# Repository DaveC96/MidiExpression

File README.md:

# MidiExpression
A hardware unit to add MIDI control to any device that takes an expression pedal input.

This is based on the Arduino Nano, and so only supports DIN MIDI. This project could easily be replicated with a Teensy or similar for USB support.

The board can be powered by:
- USB directly to the Nano
- DC barrel (centre-negative to work with guitar pedalboard PSUs)
- (Speculatively) Directly from the reference voltage on the expression input

-----

## Usage

Upon being powered on, the device will attempt to read any persistent settings. If none are found, it resets to these defaults:

| Param   | Value      |
| :---        | :---          |
| Channel | 0 (omni) |
| CC         | 4            |
| Min value | 0          |
| Max value | 127     |

These can be changed by sending a SysEx message in the following manner:

`[sysex header (0xF0)] [manufacturer ID (0x00)] [channel (0-16)] [CC] [min] [max] [sysex terminator (0xF7)]`

For example, to set channel **12**, CC **42**, with a range of **18**-**99**, the message would be (hex):

`F0 00 0C 2A 12 63 F7`

When receiving a valid sysex config message, the device will reboot to adopt the new parameters.
A hard flash reset for emergenciees can be performed by sending the following (very original) sysex message:

`F0 00 DE AD F7`

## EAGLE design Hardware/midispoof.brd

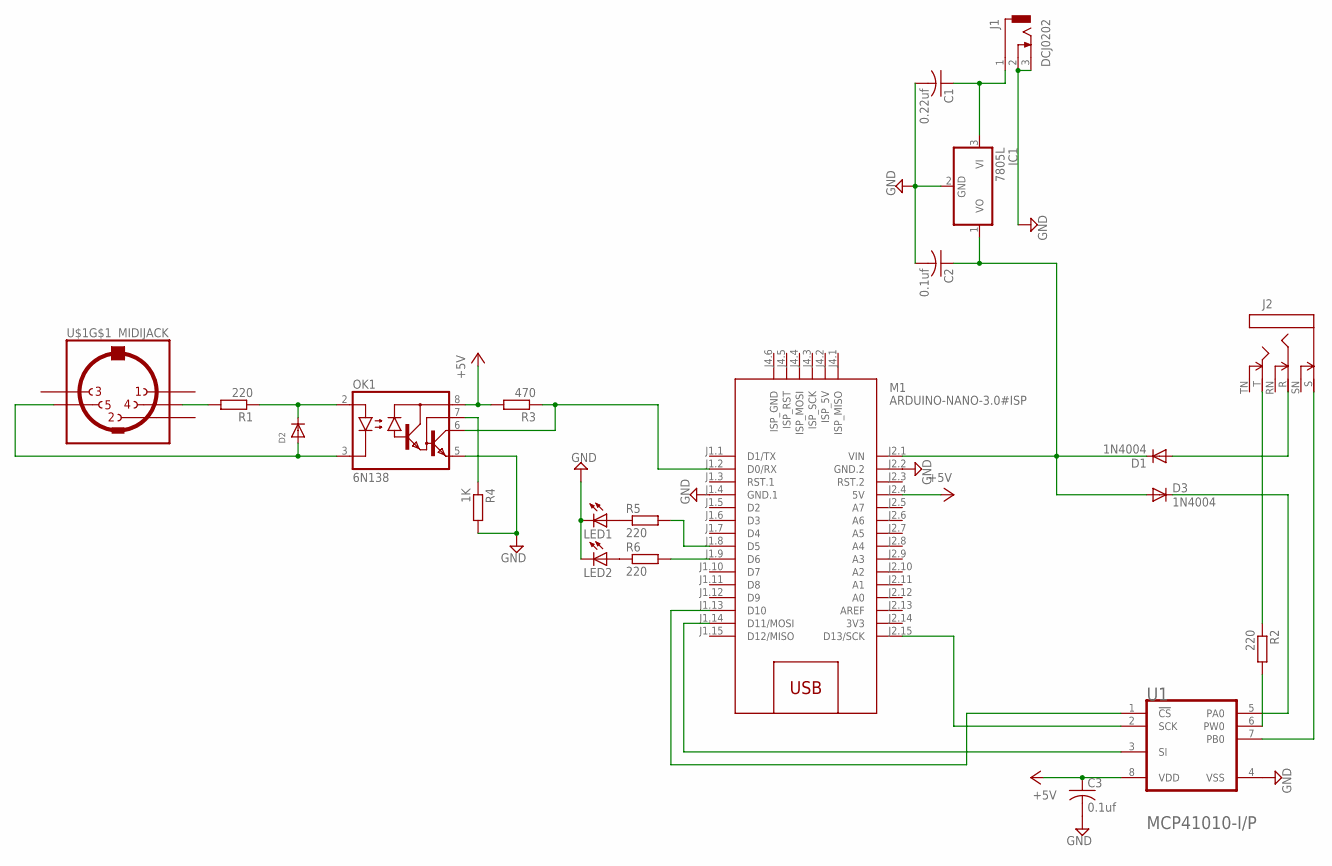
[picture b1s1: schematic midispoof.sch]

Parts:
C1: 0.22uf; C050-025X075
C2, C3: 0.1uf; C050-025X075
D1, D3: 1N4004; DO41-10
D2: DIODEDO-1N4148; DO-1N4148
IC1: 7805L; TO92
J1: DCJ0202
J2: STEREOSWS; NMJ6HC-S
LED1, LED2: LED3MM
M1: ARDUINO-NANO-3.0#ISP
OK1: 6N138; DIL08
R1, R2, R5, R6: 220; 0207/10
R3: 470; 0207/10
R4: 1K; 0207/10
U1: MICROCHIP_MCP41010-I-PMICROCHIP_MCP41010-I-P_0_0; MICROCHIP_MCP41010-I-P_0
U$1: MIDIJACK; CP-2350

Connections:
3V3: M1.J2.14 (3V3)
+5V: C3.1, M1.J2.4 (5V), OK1.8 (VCC), R3.2, U1.8 (VDD)
GND: C1.2, C2.2, C3.2, IC1.2 (GND), J1.2, J1.3, LED1.K (C), LED2.K (C), M1.J1.4 (GND.1), M1.J2.2 (GND.2), OK1.5 (GND), R4.2, U1.4 (VSS)
unnamed: M1.J2.15 (D13/SCK), U1.2 (SCK)
unnamed: C1.1, IC1.3 (VI), J1.1
unnamed: M1.J1.14 (D11/MOSI), U1.3 (SI)
unnamed: LED1.A, R5.1
unnamed: R1.2, U$1.4
unnamed: M1.J1.13 (D10), U1.1 (!CS!)
unnamed: D1.A, J2.R
unnamed: D3.C, U1.5 (PA0)
unnamed: J2.S, U1.7 (PB0)
unnamed: J2.T, R2.1
unnamed: R2.2, U1.6 (PW0)
unnamed: D2.C, OK1.2 (A), R1.1
unnamed: D2.A, OK1.3 (C), U$1.5
unnamed: M1.J1.2 (D0/RX), OK1.6 (VO), R3.1
unnamed: C2.1, D1.C, D3.A, IC1.1 (VO), M1.J2.1 (VIN)
unnamed: OK1.7 (VB), R4.1
unnamed: LED2.A, R6.1
unnamed: M1.J1.8 (D5), R5.2
unnamed: M1.J1.9 (D6), R6.2

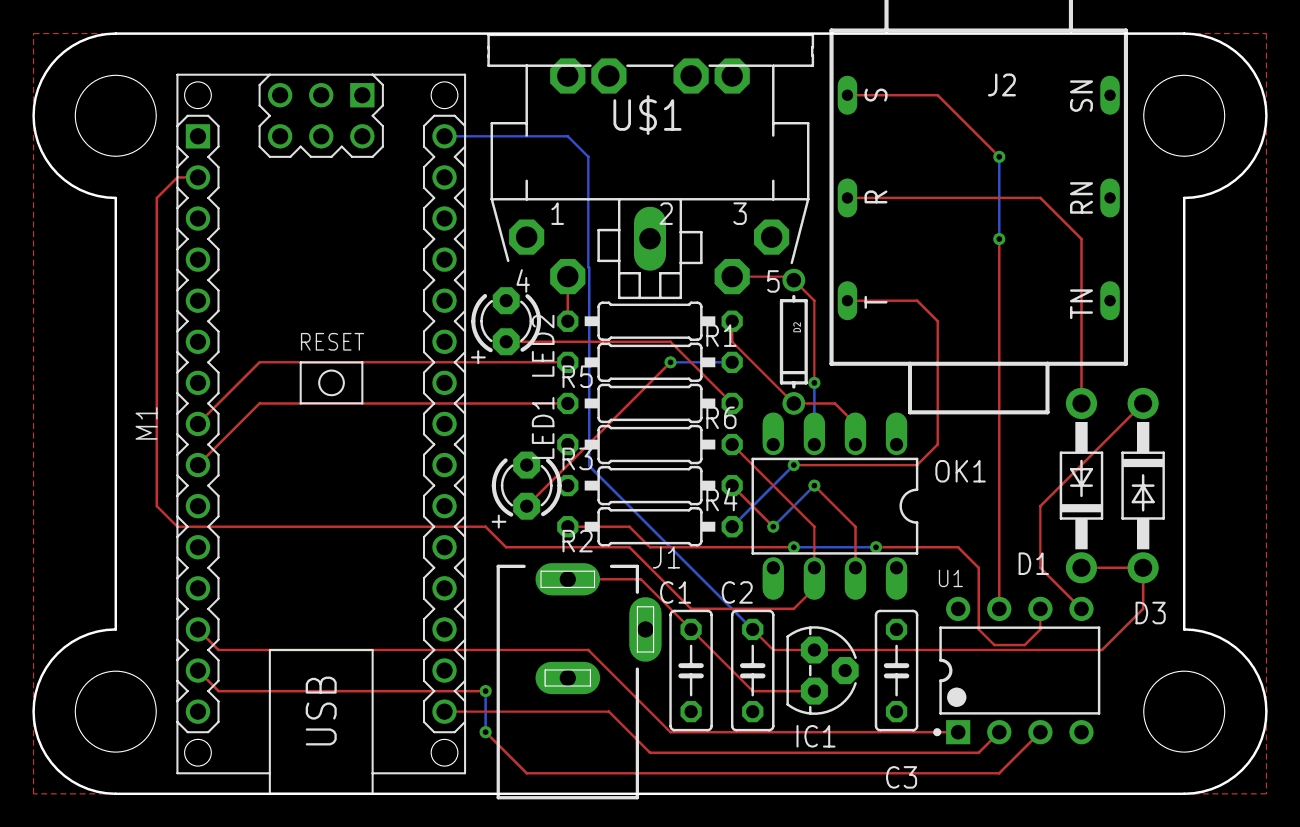
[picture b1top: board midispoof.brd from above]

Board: 2 copper layers, 76.2 x 47.0 mm, 21 parts (0 on the bottom side), 21 nets.

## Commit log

2020-12-29 Readme
2020-12-29 DEAD sysex function
2020-12-30 Model makes more sense as struct than class
2020-12-30 SPI stuff
2020-12-31 Corrected missing supply flood fills on PCB layout

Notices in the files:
parts and their libraries:
diy-modules: Released under the Creative Commons Attribution 4.0 International License: http://creativecommons.org/licenses/by/4.0
